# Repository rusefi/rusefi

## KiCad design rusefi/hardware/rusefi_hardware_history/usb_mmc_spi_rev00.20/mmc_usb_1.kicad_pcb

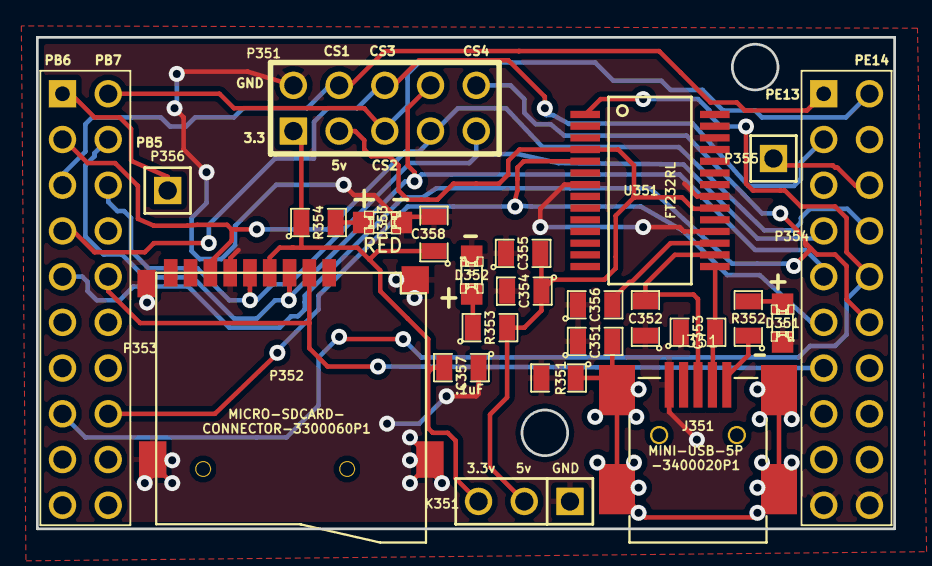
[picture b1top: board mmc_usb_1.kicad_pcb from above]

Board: 2 copper layers, 47.6 x 27.3 mm, 25 parts (1 on the bottom side), 23 nets.

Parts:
C351: 4700pF; SM0805
C352, C353: 47pF; SM0805
C354, C358: 4.7uF; SM0805
C355, C356, C357: .1uF; SM0805
D351: GREEN; LED-0805
D352, D353: RED; LED-0805
G305: LOGO; LOGO_F
J351: J351; MINI-USB-5P-3400020P1
K351: CONN_3; PIN_ARRAY_3_A
P351: CONN_5X2; PIN_ARRAY_5x2
P352: MICRO-SDCARD-CONNECTOR-3300060P1
P353, P354: CONN_10X2; PIN_ARRAY_10X2
P355, P356: CONN_1; PIN_ARRAY_1
R351: 1M; SM0805
R352, R353, R354: 1k; SM0805
U351: FT232RL; ssop-28

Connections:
/3.3V: C357.2, C358.1, K351.3, P351.1, P352.4, R354.1
/5V: C354.1, C355.2, K351.2, P351.3, R353.2, U351.4, U351.20
/CAN_TX: P353.1, P356.1
/CS1: P351.4, P353.5, P354.1
/CS2: P351.5, P353.2, P354.2
/CS3: P351.6, P353.7, P354.3
/CS4: P351.10, P353.9, P354.12
/CS_SD_MODULE: P352.2, P353.10, P354.13
/SPI_MISO: P351.7, P352.7, P353.3, P354.8
/SPI_MOSI: P351.8, P352.3, P353.4, P354.9
/SPI_SCK: P351.9, P352.5, P353.6, P354.7
/USART_RX: P353.16, P354.11, U351.5
/USART_TX: P353.15, P354.10, U351.1
GND: C351.1, C352.1, C353.1, C354.2, C355.1, C356.1, C357.1, C358.2, D351.2, D352.2, D353.2, J351.5, K351.1, P351.2, P352.6, P352.G1, P352.G2, P352.G3, P352.G4, P354.19, P354.20, R351.2, U351.7, U351.18, U351.21, U351.25, U351.26
unnamed: J351.1, R352.1
unnamed: C351.2, J351.6, R351.1
unnamed: C353.2, J351.2, U351.15
unnamed: P354.6, P355.1
unnamed: D351.1, R352.2
unnamed: C356.2, U351.17
unnamed: D352.1, R353.1
unnamed: C352.2, J351.3, U351.16
unnamed: D353.1, R354.2

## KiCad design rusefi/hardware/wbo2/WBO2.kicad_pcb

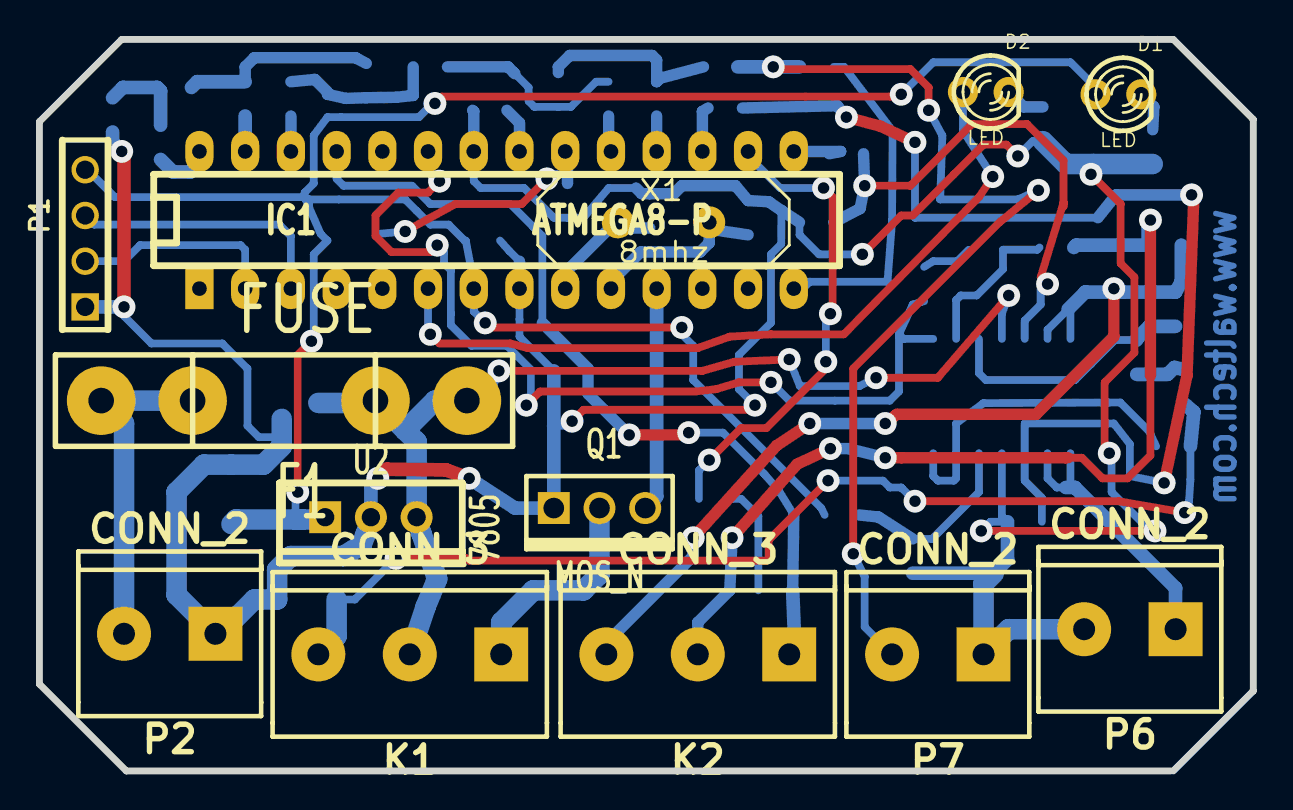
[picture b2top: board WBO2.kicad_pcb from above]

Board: 2 copper layers, 67.4 x 40.6 mm, 53 parts (0 on the bottom side), 45 nets.

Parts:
C1, C13: 10uf; SM1206
C2, C7, C15: 1uf; SM0805
C3: 22p; SM0805
C4: 229; SM0805
C5, C6: .1; SM0805
C14: .1uf; SM0805
D1, D2: LED; LED-3MM
D3: DIODE-SOT; SOT23
F1: FUSE; FUSE5-20
IC1: ATMEGA8-P; DIP-28__300_ELL
K1, K2: CONN_3; mors_3p
L1: 10mh; SM1206
P1: CONN_4; PIN_ARRAY_4x1
P2, P6, P7: CONN_2; mors_2p
Q1: MOS_N; TO220GDS
R1: 100; SM0805
R2, R9: 1.8k; SM0805
R3: 18k; SM0805
R4, R7, R8, R18, R19, R20, R21, R22, R23, R29: 10k; SM0805
R10: 6.8k; SM0805
R12: 62ohm; SM0805
R13, R14: 22k; SM0805
R15, R16: 12k; SM0805
R17, R30: 100k; SM0805
R24, R25, R26, R27, R28: 5k; SM0805
U2: 7805; TO220_VERT-reg
U4: LM324; SO14N
X1: 8mhz; HC-18UV-short

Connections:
/bit0: IC1.28, R23.2
/bit1: IC1.27, R22.2
/bit2: IC1.26, R21.2
/bit3: IC1.19, R20.2
/bit4: IC1.18, R19.2
/bit5: IC1.14, R18.2
/nernst: IC1.25, K2.1, R10.1
/pump: K2.2, R12.2, R14.2
/pump-adc: IC1.23, R17.1, U4.1
/rcal: K2.3, R12.1, R13.2, U4.6, U4.7
/vref: C13.2, K1.3, R1.1, R30.1
unnamed: C1.1, C6.2, D1.1, IC1.7, L1.2, P1.4, R3.1, U2.VO
unnamed: R13.1, R15.2, U4.3
unnamed: R23.1, R28.1, R29.2
unnamed: R22.1, R27.1, R28.2
unnamed: R21.1, R26.1, R27.2
unnamed: R20.1, R25.1, R26.2
unnamed: R19.1, R24.1, R25.2
unnamed: K1.1, Q1.D
unnamed: R14.1, R16.2, U4.2
unnamed: D2.1, IC1.6
unnamed: P6.1, U4.8, U4.9
unnamed: D2.2, R9.2
unnamed: C14.2, R10.2
unnamed: C14.1, IC1.16
unnamed: IC1.15, R7.2
unnamed: C2.1, IC1.21
unnamed: R3.2, R4.2, U4.12
unnamed: IC1.3, P1.3
unnamed: D1.2, R2.2
unnamed: F1.1, P2.2
unnamed: IC1.2, P1.2
unnamed: R1.2, U4.13, U4.14
unnamed: IC1.17, R8.2
unnamed: IC1.11, Q1.G
unnamed: R15.1, R30.2
unnamed: R16.1, R17.2
unnamed: P7.2, R18.1, R24.2
unnamed: C15.2, R7.1, U4.5
unnamed: C7.2, R8.1, U4.10
unnamed: C5.1, IC1.20, L1.1
unnamed: C4.1, IC1.10, X1.2
unnamed: C3.1, IC1.9, X1.1
VDD: D3.3, F1.2, K1.2, U2.VI, U4.4
VSS: C1.2, C2.2, C3.2, C4.2, C5.2, C6.1, C7.1, C13.1, C15.1, D3.2, IC1.8, IC1.22, P1.1, P2.1, P6.2, P7.1, Q1.S, R2.1, R4.1, R9.1, R29.1, U2.GND, U4.11
